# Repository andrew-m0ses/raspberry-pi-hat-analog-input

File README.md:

RPi Hat that accesses data from up-to-8 analog inputs using the MCP3008 chip. Python code for accessing the relevant GPIO data is also included.

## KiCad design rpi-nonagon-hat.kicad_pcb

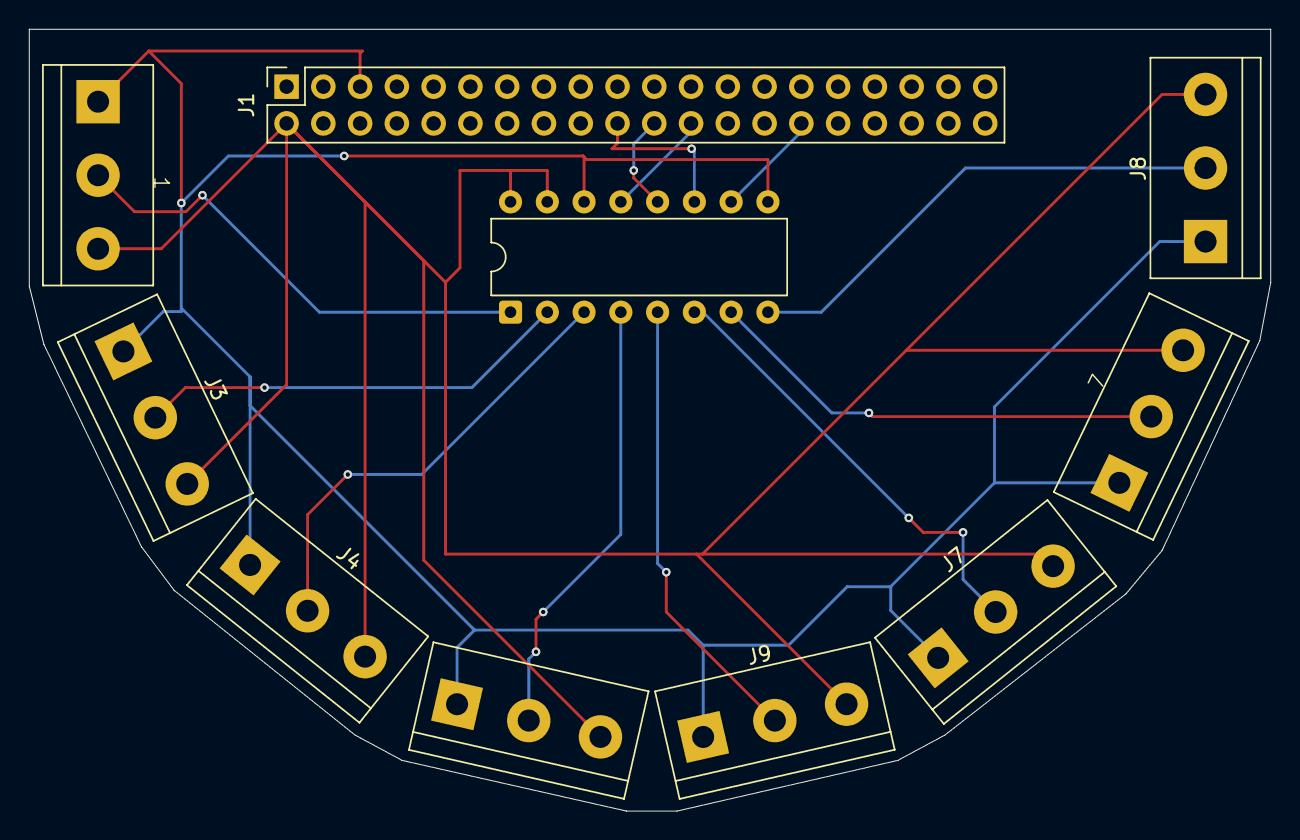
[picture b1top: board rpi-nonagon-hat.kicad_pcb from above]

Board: 2 copper layers, 85.8 x 54.0 mm, 10 parts (0 on the bottom side), 14 nets.

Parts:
J1: Conn_02x20_Odd_Even; PinSocket_2x20_P2.54mm_Vertical
J2, J3, J4, J5, J6, J7, J8, J9: Conn_01x03; TerminalBlock_bornier-3_P5.08mm
U1: MCP3008; DIP-16_W7.62mm

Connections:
unnamed: J1.2, J2.3, J3.3, J4.3, J5.3, J6.3, J7.3, J8.3, J9.3, U1.15 (Vref), U1.16 (Vdd)
unnamed: J1.5, J2.1, J3.1, J4.1, J5.1, J6.1, J7.1, J8.1, J9.1, U1.9 (DGND), U1.14 (AGND)
unnamed: J1.20, U1.11 (Din)
unnamed: J1.22, U1.12 (Dout)
unnamed: J1.24, U1.13 (CLK)
unnamed: J1.30, U1.10 (~CS/SHDN)
unnamed: J2.2, U1.1 (CH0)
unnamed: J3.2, U1.2 (CH1)
unnamed: J4.2, U1.3 (CH2)
unnamed: J5.2, U1.4 (CH3)
unnamed: J6.2, U1.7 (CH6)
unnamed: J7.2, U1.6 (CH5)
unnamed: J8.2, U1.8 (CH7)
unnamed: J9.2, U1.5 (CH4)
